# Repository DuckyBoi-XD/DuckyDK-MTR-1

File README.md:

# DuckyDK-MTR-1

### Description
This is a Metronome device called the DuckyDK MTR-1. This is for musicians, like me, who need a portable metronome that can be used anywhere. It is designed in a compact form to maximize space usage and portability.

## Kicad Schematic

## Kicad PCB

## PCB wiring (RED LINES)

(I didn't know how to make this look nice.)

## Fusion Case

## Fusion Production Case

### Inspiration
This idea was thought of and inspired when I bought a new drum kit which I loved, and I wanted to think of different projects I could make which is connected to my drum kit. One idea that was obvious was to make a custom metronome. This is the result of that idea. Even though devices like laptops can do this, I wanted to make a portable, offline metronome that is not reliant on any device and can be brought along to many places. The price of a drum metronome was also expensive, which I found weird, so I wanted to try to do it myself

**Name**
The name DuckyDK MTR-1 is from many things. **Ducky** comes from my username **Ducky**Boi_XD, **DK** is/comes from **D**rum **K**it or **D**uc**k**. **MTR** comes from **M**etronome, while the **1** indicates that this is the first version of this metronome project.

### Features 
These are the features that are implemented in the DuckyDK MTR-1:
- **Compact Design**: The device is contained in a small, portable, compact case which is custom designed to fit all the necessary components. 

- **Adjustable Tempo/Time signature**: The tempo and time signature can be adjusted to fit the user's needs. The temp can be adjusted by the rotary encoder and the time signature can be adjusted by the internal button on the rotary encoder.

- **Volume Control**: The volume of the metronome can be adjusted but the potentiometer is attached to the case. This the user to adjust their preference for their volume. For example, I play drums which can be quite loud, resulting in the need of a louder metronome.

- **2 Control Buttons**: On the case is 2 buttons controlling 2 important functions of the metronome. The first button is the start or stop mechanism of the metronome. The second button is a preset button. This button contains 3 presets that can be selected and used by pushing the preset button.

- **Info Display**: The device contains an appropriately sized OLED display which contains many necessary information. It contains, a big indicator of the current tempo/BPM in the centre of the screen, a volume level on the right side of the screen as a bar with percentage sign underneath, a 3 boxes which is the preset indicator on the left side of the screen, and lastly, the current time signature located on the bottom of the screen, under the BPM indicator.

- **Headphone Jack**: The device contains a headphone jack which allows the user to connect headphones to the device. This is currently the only way to hear the metronome. This headphone jack also contains a switch when the headphones are connected. This can be changed to do whatever you want.

### BOM (Bill of Materials)

#### NOTE
Aliexpress prices may change, all prices are based of no sales or coupons (except for hot plate), so this is the max price possible, and the final result of the price would be reduced.

(GST) = General sales tax, it's calculated at the last **GST** 
Tax is calculated at the last **TAX**

A few of these items from Digikey are extra components. This is because if I spend more than $50 from digikey, I get free shipping, which is really imporntnad because shipping to my country is expensive. I talked with [@acon](https://hackclub.slack.com/team/U04KEK4TS72) and he said if it is cheaper, then it's ok.

This BOM might have errors and be old, so check the BOM file in repo.

The BOM contains some items that are components that will help a huge amount with this project and could help future projects (Hot plate, solderer stand and tweezers.

| Component | Quantity | Description | Base Price | Extra Costs | Link | 
|-----------|----------|-------------|------------|-------------|------|
| Xiao ESP32-S3 Plus | 1 | MCU (Microcontroller Unit) (Digikey) | $7.99 | (**GST**) | https://www.digikey.co.nz/en/products/detail/seeed-technology-co-ltd/102010671/26553873 | 
| PCM5102APWR | 1 | DAC (Digital to Analog Converter) (Digikey) | $4.43 | (**GST**) | https://www.digikey.co.nz/en/products/detail/texas-instruments/PCM5102APWR/3727211?s=N4IgTCBcDaIAoGECyBWAjABjAQTgdQCUQBdAXyA |
| MAX9722AEUE+ | 1 | AMP (Audio Amplifier) (Digikey) | $1.52  | (**GST**) | https://www.digikey.co.nz/en/products/detail/analog-devices-inc-maxim-integrated/MAX9722AEUE/1495288 | 
| SJ1-3514N | 1 | 3.5mm Headphone Jack (Digikey) | $1.19  | (**GST**) | https://www.digikey.co.nz/en/products/detail/same-sky-formerly-cui-devices/sj1-3514n/738685 | 
| PTN092-H50115K1A | 1 | Potentiometer (Digikey) | $2.00  | (**GST**) | https://www.digikey.co.nz/en/products/detail/same-sky-formerly-cui-devices/PTN092-H50115K1A/24767692 |
| EC11E18244A5 | 1 | Rotary Encoder (Digikey) | $4.85 | (**GST**) | https://www.digikey.co.nz/en/products/detail/alps-alpine/ec11e18244a5/21721665 |
| 404070001 | 1 | ESD Safe Tweezers (Straight) (Digikey) | $2.50 | (**GST**) | https://www.digikey.co.nz/en/products/detail/seeed-technology-co-ltd/404070001/5488233 |
| 422 | 1 | ESD Safe Tweezers (Curved) (Digikey) | $3.95 | (**GST**) | https://www.digikey.co.nz/en/products/detail/adafruit-industries-llc/422/7241434 |
| 1007-20-1-2000-001-1-TD | 25 feet | Wires | $11.87 | (**GST**) | https://www.digikey.co.nz/en/products/detail/cnc-tech/1007-20-1-2000-001-1-TD/17799227 |
| 20-0600-21 | 2 (20 pins each) | Male pin headers | $7.66 | (**GST**) | https://www.digikey.co.nz/en/products/detail/aries-electronics/20-0600-21/4207162 |
| 97790603211 | 10 | Screws | $2.58 | (**GST**) | https://www.digikey.co.nz/en/products/detail/w%C3%BCrth-elektronik/97790603211/10056392 |
| 97791003111 | 10 | Screws | $2.24 | (**GST**) $7.92 | https://www.digikey.co.nz/en/products/detail/w%C3%BCrth-elektronik/97791003111/10056389 | 
| 1.3 Inch Oled Module Witte Kleur | 1 | OLED screen 4 pin (Aliexpress) | $5.40 | (**TAX**) | https://www.aliexpress.com/item/1005007451015054.html?spm=a2g0o.productlist.main.3.5c94BkFLBkFLwI&algo_pvid=c05ab788-0f62-4cac-8ecf-0ac50b96f1c8&algo_exp_id=c05ab788-0f62-4cac-8ecf-0ac50b96f1c8-2&pdp_ext_f=%7B%22order%22%3A%221408%22%2C%22eval%22%3A%221%22%7D&pdp_npi=4%40dis%21NZD%215.36%211.68%21%21%213.15%210.99%21%402103247917505815500323989e2c7f%2112000040806152742%21sea%21NZ%216394433987%21ABX&curPageLogUid=4GgHuLqPJwAs&utparam-url=scene%3Asearch%7Cquery_from%3A |
| Ultra Short Switch | 2 | Buttons No LED 3-6V 16mm black momentary (Aliexpress)| $9.34 | (**TAX**) | https://www.aliexpress.com/item/1005004920346156.html?spm=a2g0o.productlist.main.7.7f7d5f2722dp5N&algo_pvid=88ea1ebf-ed98-4122-ae48-2b34d2cbcef4&algo_exp_id=88ea1ebf-ed98-4122-ae48-2b34d2cbcef4-6&pdp_ext_f=%7B%22order%22%3A%221272%22%2C%22eval%22%3A%221%22%7D&pdp_npi=4%40dis%21NZD%214.19%211.70%21%21%2117.53%217.11%21%402103247417506694259818233e29c3%2112000039500055503%21sea%21NZ%216394433987%21ABX&curPageLogUid=AdxbPFQrTg6S&utparam-url=scene%3Asearch%7Cquery_from%3A |
| Hexagon Fine Thread Thin Nuts | 1 M7 (20 pieces) | Nuts for Rotary encoders and Potentiometer (Aliexpress) | $3.84 | (**TAX**) + $5.49 (Shipping) | https://www.aliexpress.com/item/1005006173995318.html?spm=a2g0o.productlist.main.15.7dbd4ebaNansD7&algo_pvid=bbffa5d8-f689-4588-a6f6-ce0996436945&algo_exp_id=bbffa5d8-f689-4588-a6f6-ce0996436945-14&pdp_ext_f=%7B%22order%22%3A%22151%22%2C%22eval%22%3A%221%22%7D&pdp_npi=4%40dis%21NZD%211.85%211.39%21%21%217.88%215.91%21%40210308a417510851180067032e73ba%2112000036120140725%21sea%21NZ%216394433987%21ABX&curPageLogUid=mVYjfbvrU5vv&utparam-url=scene%3Asearch%7Cquery_from%3A |
| Brass melting heat insert | 1 M3 OD 5mm length 5mm (50 pieces) (Aliexpress) | Heat inserts for case and PCB (Aliexpress) | $4.71 | (**TAX**) | https://www.aliexpress.us/item/1005003582355741.html?spm=a2g0o.productlist.main.5.24ac12d7m7D9Ol&algo_pvid=870e099a-1be4-4b3b-9495-46eae48c9ac9&algo_exp_id=870e099a-1be4-4b3b-9495-46eae48c9ac9-4&pdp_ext_f=%7B%22order%22%3A%2218759%22%2C%22eval%22%3A%221%22%7D&pdp_npi=4%40dis%21NZD%213.79%211.66%21%21%212.26%210.99%21%402103244b17515900105603223eeccf%2112000026370649721%21sea%21NZ%216394433987%21ABX&curPageLogUid=PvX1sJbDEX6O&utparam-url=scene%3Asearch%7Cquery_from%3A |
| Mini Micarta Soldering Iron Stand Holder | 1 | Soldering stand for Pinecil (Aliexpress) | $3.21 | (**TAX**) | https://www.aliexpress.com/item/1005006352272696.html?spm=a2g0o.store_pc_home.promoteRecommendProducts_2004652237334.1005006352272696 | 
| Type-C Mini Hot Plate PCB SMD | 1 | Hot plate for small components (Aliexpress)| $2.85 | (**TAX**) | https://www.aliexpress.com/item/1005006511319731.html?spm=a2g0o.productlist.main.1.60d741e0IoXroY&algo_pvid=6e3b7f9e-e587-4607-8ce7-bc63e0be9c8f&algo_exp_id=6e3b7f9e-e587-4607-8ce7-bc63e0be9c8f-0&pdp_ext_f=%7B%22order%22%3A%221244%22%2C%22eval%22%3A%221%22%7D&pdp_npi=4%40dis%21NZD%2147.35%212.35%21%21%21201.83%219.99%21%402103277f17516748696561900e3da4%2112000037477574263%21sea%21NZ%216394433987%21ABX&curPageLogUid=GBlzTiUO8Kkx&utparam-url=scene%3Asearch%7Cquery_from%3A |
| Monolithic Ceramic Capacitor Kit | 1 | Ceramic Capacitor kit  0.1uf - 10uf  500 pcs (Aliexpress) | $10.93 | (**TAX**) | https://www.aliexpress.com/item/1005006772301578.html?spm=a2g0o.productlist.main.32.28fd4d9dNmQm8b&algo_pvid=481dbf38-0228-437b-89a1-11371636bc9c&aem_p4p_detail=2025070516251011559118486215700004231565&algo_exp_id=481dbf38-0228-437b-89a1-11371636bc9c-25&pdp_ext_f=%7B%22order%22%3A%2268%22%2C%22eval%22%3A%221%22%7D&pdp_npi=4%40dis%21NZD%2110.93%211.66%21%21%216.50%210.99%21%402101effb17517579108254835e8b56%2112000038249154392%21sea%21NZ%216394433987%21ABX&curPageLogUid=EixJBf52480q&utparam-url=scene%3Asearch%7Cquery_from%3A&search_p4p_id=2025070516251011559118486215700004231565_7 | 
| Electrolytic Capacitor Kit | 1 | Aluminium Electrolytic Capacitors Kit 1uf - 470uf 120 pcs (Aliexpress) | $5.82 | (**TAX**) | https://www.aliexpress.com/item/1005005626707702.html?spm=a2g0o.productlist.main.1.33696zwd6zwdiq&algo_pvid=888a458f-cf4b-4112-82b8-b34241255c81&algo_exp_id=888a458f-cf4b-4112-82b8-b34241255c81-0&pdp_ext_f=%7B%22order%22%3A%221412%22%2C%22eval%22%3A%221%22%7D&pdp_npi=4%40dis%21NZD%215.82%211.66%21%21%2124.81%217.08%21%402101ea7117517609208091735e0dee%2112000033796706983%21sea%21NZ%216394433987%21ABX&curPageLogUid=mk4afSyCFG9E&utparam-url=scene%3Asearch%7Cquery_from%3A |
| Resistor Kit | 1 | Metal Film Resistor Pack Assorted Kit 10ohm - 1m ohm 300pcs (Aliexpress) | $4.47 | (**TAX**) $9.08 | https://www.aliexpress.com/item/1005005855324735.html?spm=a2g0o.productlist.main.1.1b22578fKSCLRh&algo_pvid=85089809-d842-4483-bf22-11a567e35ac0&algo_exp_id=85089809-d842-4483-bf22-11a567e35ac0-0&pdp_ext_f=%7B%22order%22%3A%223547%22%2C%22eval%22%3A%221%22%7D&pdp_npi=4%40dis%21NZD%214.35%211.66%21%21%212.59%210.99%21%402101e07217517039549628903eb221%2112000034587357832%21sea%21NZ%216394433987%21ABX&curPageLogUid=GUVoHuNTQhAN&utparam-url=scene%3Asearch%7Cquery_from%3A |
| PCB | 5 | Custom PCB I made | $2.00 | $6.40 | N/A (CUSTOM JLCPCB) |
| Printing Legion | 1 | 3d printed case | $5.00 | N/A | N/A (CUSTOM PRINT) |
| Total: | $109.85 (BASE COMPONENTS TOTAL) | $138.42 (ALL TOTAL) | 
|--------|---------------------------------|---------------------|
### Construction
The DuckyDK MTR-1 was mainly made using Kicad, Fusion 360, Github and Slack. I made all the PCB schematics and design of the PCB in Kicad, while I made the 3D model of the case in Fusion 360. I used GitHub to document my process of making the project and Slack to help me answer questions. I spent a lot of time researching and reading through data sheets and answers to questions to figure out new things I didn't understand. I learnt a lot through this project, and I hope people can see and understand.

Time spent: 83 hours

### Credit
Cheers to all these people for helping make this project possible.

- [@Ryan Green](https://hackclub.slack.com/team/U090854913L): For helping me understand how to source parts and pick out a few parts for me to use.
- [@Person20020 (Koji)](https://hackclub.slack.com/team/U07QNKS5SKA): For helping me with PCB problems even when he's mainly helps with HackPad problems, also he helped with my HackPad.
- [@QinCai](https://hackclub.slack.com/team/U07BNRCEARM): For helping me answer questions and creating the code part of the project.
- [@Niko](https://hackclub.slack.com/team/U07960MD940): For helping answer importing questions about 3d printing and potentally printing my project.
- [Rudy](https://hackclub.slack.com/team/U079HV9PTC7): For helping with lots of different parts like questions and help picking out the Xiao ESP32 S3. Also, for giving my tips on picking out parts.
- [@alexren](https://hackclub.slack.com/team/U06PR6B8D37) and [@acon](https://hackclub.slack.com/team/U04KEK4TS72): For being great event organisers and creating Highway for me to do this.
- Whoever is looking over the project: I hope you enjoy reading all this. Thanks for your feedback once you finish.
- The Slack Community: For helping me answer strange and different questions to help me continue with my project.

Digikey's BOM part needs to be over $50 USD for free shipping. This is really important because shipping to my country is very expensive.

Side tangent, I'm still mad that my time from SoM is useless and especially because they announced it once I almost finished the project.

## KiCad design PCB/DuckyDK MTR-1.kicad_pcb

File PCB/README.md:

# Note

These are the files of the PCB. **.pcb** is the PCB editor, **.sch** is the schematics of the PCB, **.pro** is the file to see both files in the Kicad menu.

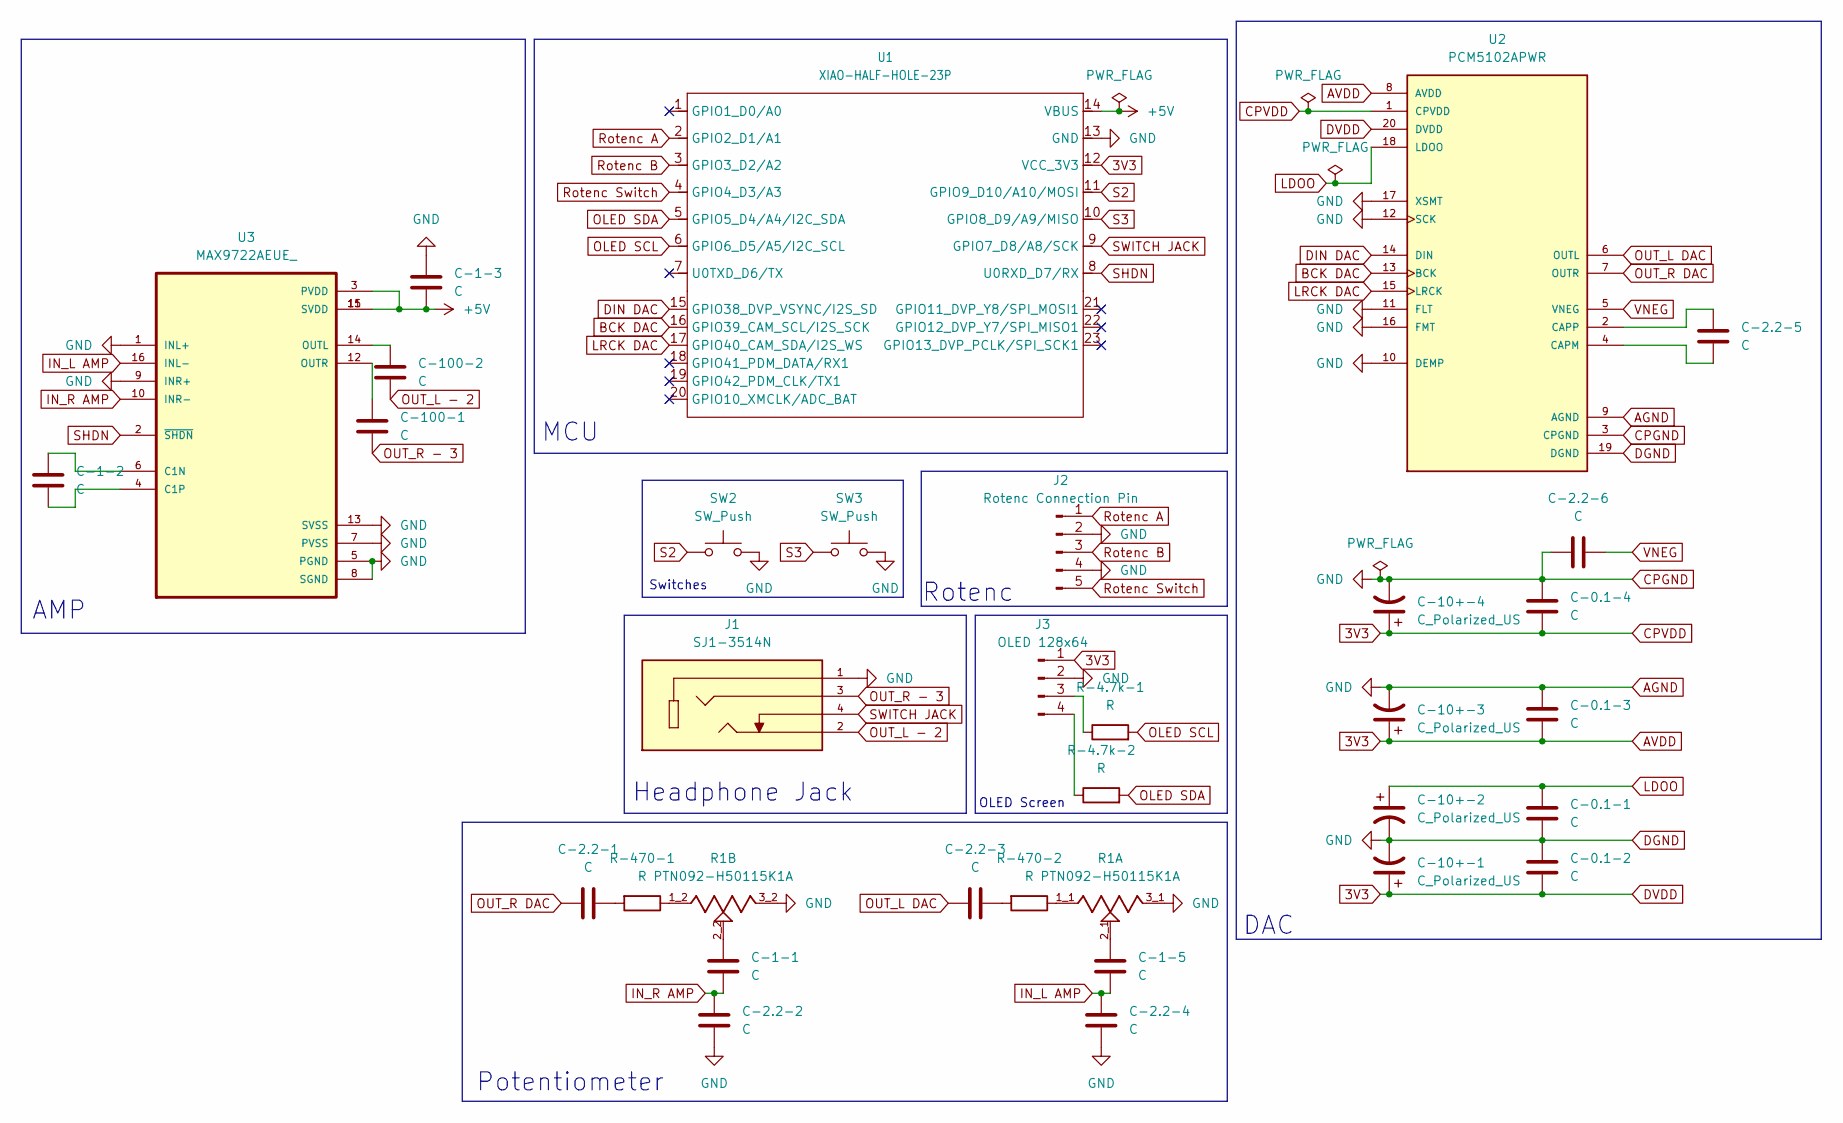
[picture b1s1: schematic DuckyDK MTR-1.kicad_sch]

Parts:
C-0.1-1, C-0.1-2, C-0.1-3, C-0.1-4, C-1-1, C-1-2, C-1-3, C-1-5, C-2.2-1, C-2.2-2, C-2.2-3, C-2.2-4, C-2.2-5, C-2.2-6: C; C_Disc_D5.0mm_W2.5mm_P5.00mm
C-10+-1, C-10+-2, C-10+-3, C-10+-4: C_Polarized_US; CP_Radial_D5.0mm_P2.00mm
C-100-1, C-100-2: C; CP_Radial_D5.0mm_P2.00mm
J1: SJ1-3514N; CUI_SJ1-3514N; PARTREV 1.02
J2: Rotenc Connection Pin; PinHeader_1x05_P2.54mm_Vertical
J3: OLED 128x64; PinHeader_1x04_P2.54mm_Vertical
R1: PTN092-H50115K1A; TRIM_PTN092-H50115K1A; PARTREV 1.01
R-4.7k-1, R-4.7k-2, R-470-1, R-470-2: R; R_Axial_DIN0207_L6.3mm_D2.5mm_P7.62mm_Horizontal
SW2, SW3: SW_Push; PinHeader_1x02_P2.54mm_Vertical
U1: XIAO-HALF-HOLE-23P; MOUDLE23P-SMD-2.54-21X17.8MM.kicad_mod.kicad_sym
U2: PCM5102APWR; SOP65P640X120-20N; PARTREV C; DigiKey_Part_Number 296-36707-2-ND
U3: MAX9722AEUE_; SOP65P640X110-16N; DigiKey_Part_Number MAX9722AEUE+-ND

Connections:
3V3: C-0.1-2.2, C-0.1-3.2, C-0.1-4.2, C-10+-1.1, C-10+-3.1, C-10+-4.1, J3.1, U1.12 (VCC_3V3), U2.1 (CPVDD), U2.8 (AVDD), U2.20 (DVDD)
+5V: C-1-3.2, U1.14 (VBUS), U3.3 (PVDD), U3.11 (SVDD), U3.15 (SVDD)
AGND: C-0.1-1.2, C-0.1-2.1, C-0.1-3.1, C-0.1-4.1, C-1-3.1, C-2.2-2.2, C-2.2-4.2, C-2.2-6.1, C-10+-1.2, C-10+-2.2, C-10+-3.2, C-10+-4.2, J1.1, J2.2, J2.4, J3.2, R1.3_1, R1.3_2, SW2.2, SW3.2, U1.13 (GND), U2.3 (CPGND), U2.9 (AGND), U2.10 (DEMP), U2.11 (FLT), U2.12 (SCK), U2.16 (FMT), U2.17 (XSMT), U2.19 (DGND), U3.1 (INL+), U3.5 (PGND), U3.7 (PVSS), U3.8 (SGND), U3.9 (INR+), U3.13 (SVSS)
BCK DAC: U1.16 (GPIO39_CAM_SCL/I2S_SCK), U2.13 (BCK)
DIN DAC: U1.15 (GPIO38_DVP_VSYNC/I2S_SD), U2.14 (DIN)
IN_L AMP: C-1-5.2, C-2.2-4.1, U3.16 (INL-)
IN_R AMP: C-1-1.2, C-2.2-2.1, U3.10 (INR-)
LDOO: C-0.1-1.1, C-10+-2.1, U2.18 (LDOO)
LRCK DAC: U1.17 (GPIO40_CAM_SDA/I2S_WS), U2.15 (LRCK)
unnamed: C-1-1.1, R1.2_2
unnamed: C-1-5.1, R1.2_1
unnamed: C-2.2-1.1, R-470-1.2
unnamed: C-2.2-3.1, R-470-2.2
unnamed: J3.3, R-4.7k-1.1
unnamed: J3.4, R-4.7k-2.1
unnamed: R1.1_2, R-470-1.1
unnamed: R1.1_1, R-470-2.1
unnamed: C-2.2-5.2, U2.4 (CAPM)
unnamed: C-2.2-5.1, U2.2 (CAPP)
unnamed: C-1-2.1, U3.6 (C1N)
unnamed: C-1-2.2, U3.4 (C1P)
unnamed: C-100-2.1, U3.14 (OUTL)
unnamed: C-100-1.2, U3.12 (OUTR)
OLED SCL: R-4.7k-1.2, U1.6 (GPIO6_D5/A5/I2C_SCL)
OLED SDA: R-4.7k-2.2, U1.5 (GPIO5_D4/A4/I2C_SDA)
OUT_L - 2: C-100-2.2, J1.2
OUT_L DAC: C-2.2-3.2, U2.6 (OUTL)
OUT_R - 3: C-100-1.1, J1.3
OUT_R DAC: C-2.2-1.2, U2.7 (OUTR)
Rotenc A: J2.1, U1.2 (GPIO2_D1/A1)
Rotenc B: J2.3, U1.3 (GPIO3_D2/A2)
Rotenc Switch: J2.5, U1.4 (GPIO4_D3/A3)
S2: SW2.1, U1.11 (GPIO9_D10/A10/MOSI)
S3: SW3.1, U1.10 (GPIO8_D9/A9/MISO)
SHDN: U1.8 (U0RXD_D7/RX), U3.2 (~SHDN)
SWITCH JACK: J1.4, U1.9 (GPIO7_D8/A8/SCK)
VNEG: C-2.2-6.2, U2.5 (VNEG)

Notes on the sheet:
Headphone Jack
OLED Screen
Rotenc
AMP
Switches
DAC
Potentiometer
MCU

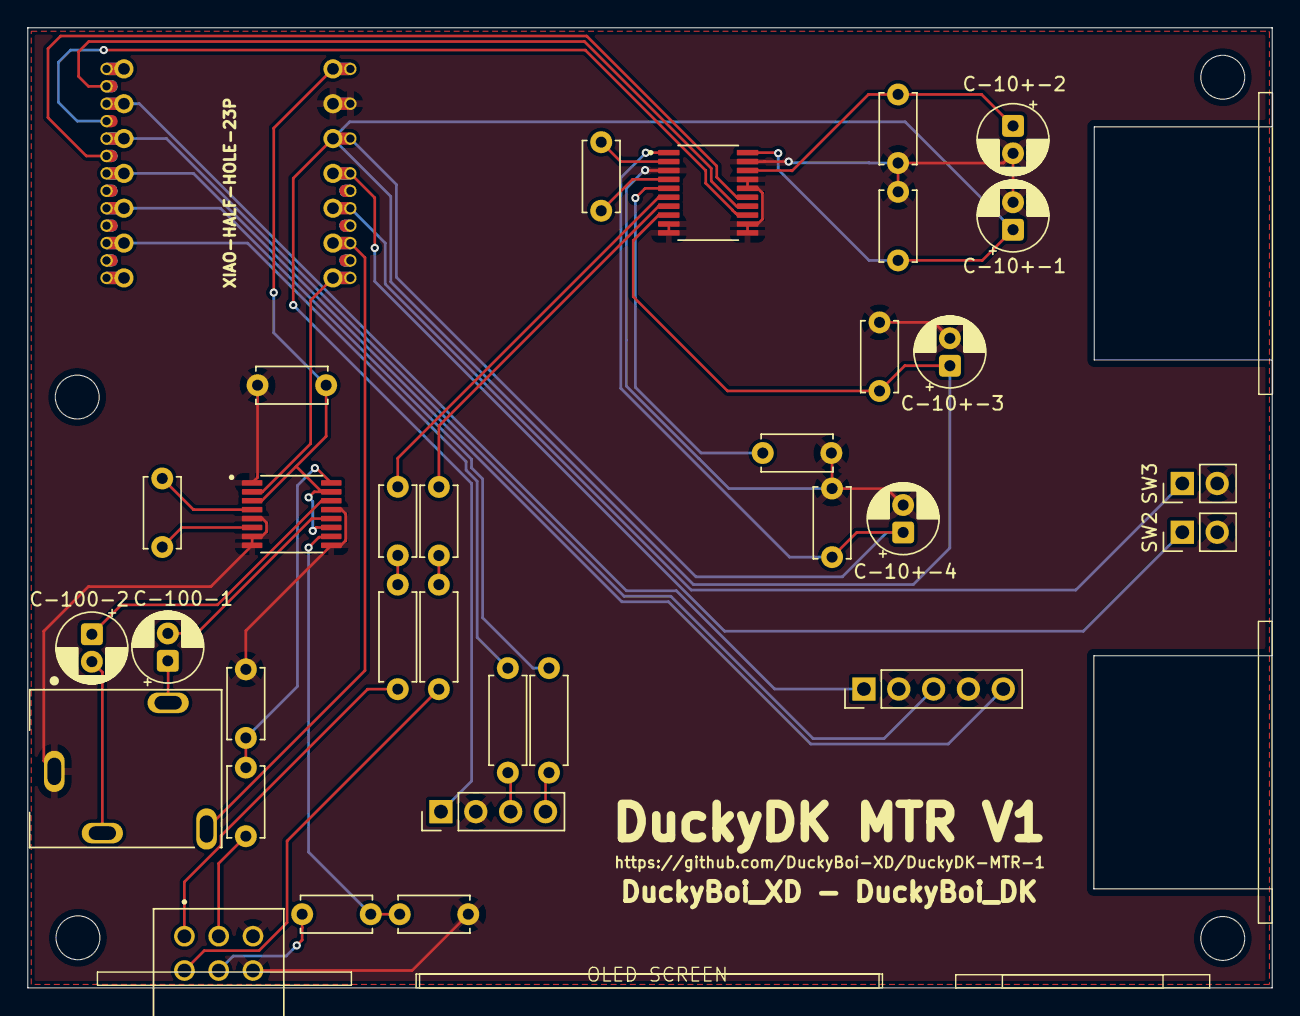
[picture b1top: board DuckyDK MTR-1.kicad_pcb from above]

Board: 2 copper layers, 90.7 x 70.0 mm, 33 parts (0 on the bottom side), 37 nets.

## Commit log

2025-06-07 Create JOURNAL.md and added titles info
2025-06-07 fix format
2025-06-08 Update JOURNAL.md semi finished
2025-06-08 Update JOURNAL.md MCU choice finish
2025-06-08 Update JOURNAL.md OLED semi
2025-06-09 Update JOURNAL.md Added headphone jack and update mcu
2025-06-10 Update JOURNAL.md Revamped and fixed everything + time (not done)
2025-06-10 Update JOURNAL.md Finsihed revamp
2025-06-11 Update JOURNAL.md june 10
2025-06-13 Update JOURNAL.md june 13???
2025-06-14 Update JOURNAL.md photo fix
2025-06-14 Update JOURNAL.md JUNE 14 YAY FINISHED EARLY
2025-06-14 Update JOURNAL.md Info updated
2025-06-16 Update JOURNAL.md June 15 + update repo
2025-06-16 Update JOURNAL.md JUNE 16 update not finished
2025-06-17 Update JOURNAL.md June 16
2025-06-18 Update JOURNAL.md june 18
2025-06-20 Update JOURNAL.md June 20 HOLIDAY
2025-06-22 Update JOURNAL.md 21 junes semi
2025-06-22 Update JOURNAL.md june 21
2025-06-22 Update JOURNAL.md photos added
2025-06-22 Update June 21 MCU finish
2025-06-23 Update journal june 22 writing
2025-06-23 Update JOURNAL.md pictures
2025-06-23 Update fix spelling
2025-06-23 Fixed?
2025-06-24 Update featues june 24
2025-06-24 Update June 23
2025-06-24 Update added title, started June 24
2025-06-24 Update June 24 finished
2025-06-24 added bit text
2025-06-24 Update june 24
2025-06-25 Update June 25 finish
2025-06-26 Update june 26
2025-06-27 add mpy file
2025-06-28 Update June 28
2025-06-30 Update June 30
2025-06-30 Update thoughts part fixed
2025-07-01 Update July 1
2025-07-02 Update July 2
2025-07-03 Update July 3, Started read me
2025-07-04 Create Cad folder, README.md file
2025-07-04 Create PCB folder, README.md file
2025-07-04 Create Production folder, README.md file
2025-07-04 Update July 4, Update read me with more info and BOM chart.
2025-07-04 Update confusion
2025-07-05 Uploaded BOM file
2025-07-05 Uploaded PCB files
2025-07-05 Update JOURNAL.md July 5
2025-07-05 Update JOURNAL.md July 5 update
2025-07-05 remove ur symlink folder
2025-07-06 Update README.md production
2025-07-06 Update README.md PCB
2025-07-06 Create README.md MPY
2025-07-06 Update README.md CAD
2025-07-06 Update JOURNAL.md Juy 6
2025-07-08 update comments and fix a few typos
2025-07-08 update comments
2025-07-08 add license
2025-07-08 imports (save 1 line), fix time signature, optimise OLED updates stuff
2025-07-08 comment out unused machine import
2025-07-08 remove unnecessary comments
2025-07-08 clarify comment . time signature button
2025-07-08 fix a bit of formating. looks much better now IMO
2025-07-24 Update JOURNAL.md
    Changed hours, cut half
